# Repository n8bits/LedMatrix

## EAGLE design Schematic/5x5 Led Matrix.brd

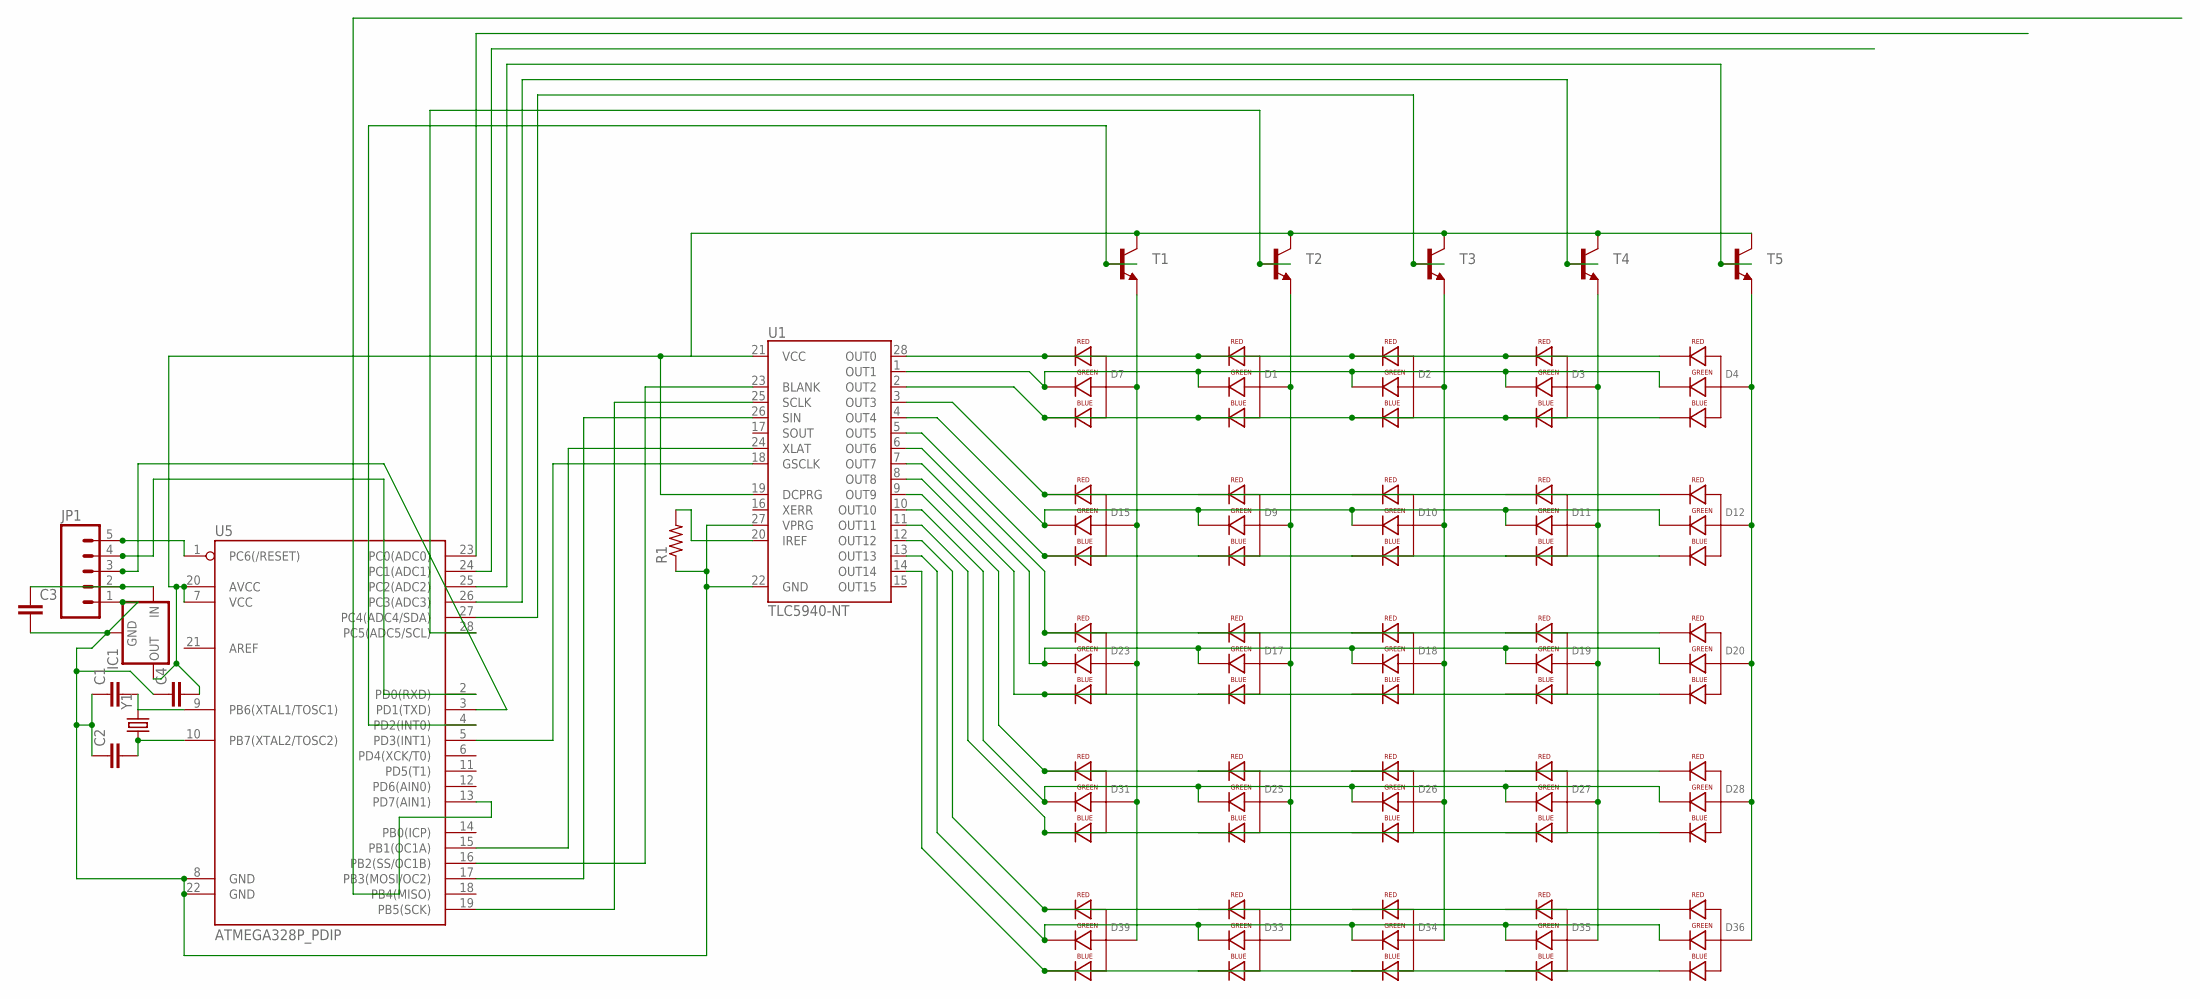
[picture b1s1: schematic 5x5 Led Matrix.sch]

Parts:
C1, C2, C3, C4: CAPPTH; CAP-PTH-SMALL
D1, D2, D3, D4, D9, D10, D11, D12, D15, D17, D18, D19, D20, D23, D25, D26, D27, D31, D33, D34, D35, D36, D39: LED-RGB-CA-THRUDIFFUSE; LED-RGB-THRU
D7, D28: LED-RGB-CA-THRUCLEAR; LED-RGB-THRU
IC1: V_REG_78XXSIDE; 78XXL
JP1: M05PTH; 1X05
R1: RESISTORPTH-1/2W; AXIAL-0.5
T1, T2, T3, T4, T5: TRANSISTOR_NPN2N3904; TO-92
U1: TLC5940-NT; DIL28-3
U5: ATMEGA328P_PDIP; DIL28-3
Y1: CRYSTALHC49US; HC49US

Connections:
GND: C1.1, C2.1, C3.2, C4.1, IC1.GND, JP1.1, R1.P$1 (1), U1.22 (GND), U1.27 (VPRG), U5.8 (GND), U5.22 (GND)
unnamed: D1.1 (RED_CATHODE), D2.1 (RED_CATHODE), D3.1 (RED_CATHODE), D4.1 (RED_CATHODE), D7.1 (RED_CATHODE), U1.28 (OUT0)
unnamed: C1.2, U5.9 (PB6(XTAL1/TOSC1)), Y1.2
unnamed: C2.2, U5.10 (PB7(XTAL2/TOSC2)), Y1.1
unnamed: JP1.5, U5.1 (PC6(/RESET))
unnamed: JP1.4, U5.2 (PD0(RXD))
unnamed: JP1.3, U5.3 (PD1(TXD))
unnamed: D1.4 (BLUE_CATHODE), D2.4 (BLUE_CATHODE), D3.4 (BLUE_CATHODE), D4.4 (BLUE_CATHODE), D7.4 (BLUE_CATHODE), U1.2 (OUT2)
unnamed: U1.25 (SCLK), U5.19 (PB5(SCK))
unnamed: U1.26 (SIN), U5.17 (PB3(MOSI/OC2))
unnamed: R1.P$2 (2), U1.20 (IREF)
unnamed: U1.24 (XLAT), U5.15 (PB1(OC1A))
unnamed: T5.2 (B), U5.25 (PC2(ADC2))
unnamed: U1.18 (GSCLK), U5.5 (PD3(INT1))
unnamed: T4.2 (B), U5.26 (PC3(ADC3))
unnamed: T3.2 (B), U5.27 (PC4(ADC4/SDA))
unnamed: T2.2 (B), U5.28 (PC5(ADC5/SCL))
unnamed: T1.2 (B), U5.4 (PD2(INT0))
unnamed: D1.3 (GREEN_CATHODE), D2.3 (GREEN_CATHODE), D3.3 (GREEN_CATHODE), D4.3 (GREEN_CATHODE), D7.3 (GREEN_CATHODE), U1.1 (OUT1)
unnamed: U1.23 (BLANK), U5.16 (PB2(SS/OC1B))
unnamed: D9.1 (RED_CATHODE), D10.1 (RED_CATHODE), D11.1 (RED_CATHODE), D12.1 (RED_CATHODE), D15.1 (RED_CATHODE), U1.3 (OUT3)
unnamed: D9.4 (BLUE_CATHODE), D10.4 (BLUE_CATHODE), D11.4 (BLUE_CATHODE), D12.4 (BLUE_CATHODE), D15.4 (BLUE_CATHODE), U1.5 (OUT5)
unnamed: D9.3 (GREEN_CATHODE), D10.3 (GREEN_CATHODE), D11.3 (GREEN_CATHODE), D12.3 (GREEN_CATHODE), D15.3 (GREEN_CATHODE), U1.4 (OUT4)
unnamed: D2.2 (ANODE), D10.2 (ANODE), D18.2 (ANODE), D26.2 (ANODE), D34.2 (ANODE), T3.1 (E)
unnamed: D17.1 (RED_CATHODE), D18.1 (RED_CATHODE), D19.1 (RED_CATHODE), D20.1 (RED_CATHODE), D23.1 (RED_CATHODE), U1.6 (OUT6)
unnamed: D17.4 (BLUE_CATHODE), D18.4 (BLUE_CATHODE), D19.4 (BLUE_CATHODE), D20.4 (BLUE_CATHODE), D23.4 (BLUE_CATHODE), U1.8 (OUT8)
unnamed: D17.3 (GREEN_CATHODE), D18.3 (GREEN_CATHODE), D19.3 (GREEN_CATHODE), D20.3 (GREEN_CATHODE), D23.3 (GREEN_CATHODE), U1.7 (OUT7)
unnamed: D25.1 (RED_CATHODE), D26.1 (RED_CATHODE), D27.1 (RED_CATHODE), D28.1 (RED_CATHODE), D31.1 (RED_CATHODE), U1.9 (OUT9)
unnamed: D25.4 (BLUE_CATHODE), D26.4 (BLUE_CATHODE), D27.4 (BLUE_CATHODE), D28.4 (BLUE_CATHODE), D31.4 (BLUE_CATHODE), U1.11 (OUT11)
unnamed: D25.3 (GREEN_CATHODE), D26.3 (GREEN_CATHODE), D27.3 (GREEN_CATHODE), D28.3 (GREEN_CATHODE), D31.3 (GREEN_CATHODE), U1.10 (OUT10)
unnamed: C3.1, IC1.IN, JP1.2
unnamed: D33.1 (RED_CATHODE), D34.1 (RED_CATHODE), D35.1 (RED_CATHODE), D36.1 (RED_CATHODE), D39.1 (RED_CATHODE), U1.12 (OUT12)
unnamed: D33.4 (BLUE_CATHODE), D34.4 (BLUE_CATHODE), D35.4 (BLUE_CATHODE), D36.4 (BLUE_CATHODE), D39.4 (BLUE_CATHODE), U1.14 (OUT14)
unnamed: D33.3 (GREEN_CATHODE), D34.3 (GREEN_CATHODE), D35.3 (GREEN_CATHODE), D36.3 (GREEN_CATHODE), D39.3 (GREEN_CATHODE), U1.13 (OUT13)
unnamed: D1.2 (ANODE), D9.2 (ANODE), D17.2 (ANODE), D25.2 (ANODE), D33.2 (ANODE), T2.1 (E)
unnamed: D4.2 (ANODE), D12.2 (ANODE), D20.2 (ANODE), D28.2 (ANODE), D36.2 (ANODE), T5.1 (E)
unnamed: D3.2 (ANODE), D11.2 (ANODE), D19.2 (ANODE), D27.2 (ANODE), D35.2 (ANODE), T4.1 (E)
unnamed: D7.2 (ANODE), D15.2 (ANODE), D23.2 (ANODE), D31.2 (ANODE), D39.2 (ANODE), T1.1 (E)
VCC: C4.2, IC1.OUT, T1.3 (C), T2.3 (C), T3.3 (C), T4.3 (C), T5.3 (C), U1.19 (DCPRG), U1.21 (VCC), U5.7 (VCC), U5.20 (AVCC)

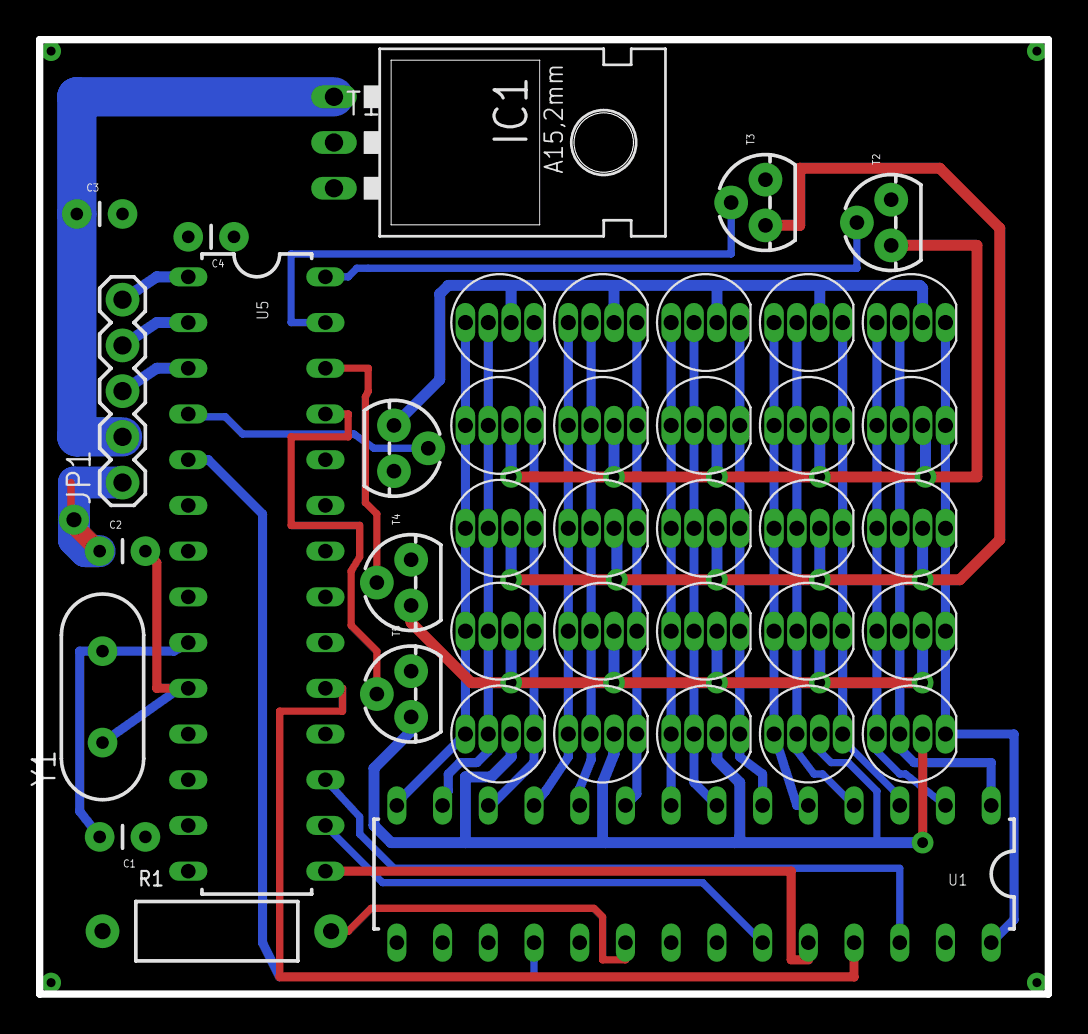
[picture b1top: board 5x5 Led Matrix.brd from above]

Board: 2 copper layers, 56.0 x 53.0 mm, 41 parts (0 on the bottom side), 39 nets.

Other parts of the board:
DRILEGEND: DRILEGEND

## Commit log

2020-06-12 Uploading to GitHub

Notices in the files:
parts and their libraries:
SparkFun-DigitalIC: Licensing: Creative Commons ShareAlike 4.0 International - https://creativecommons.org/licenses/by-sa/4.0
